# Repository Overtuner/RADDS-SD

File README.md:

# RADDS-SD
Adapter Board for RADDS

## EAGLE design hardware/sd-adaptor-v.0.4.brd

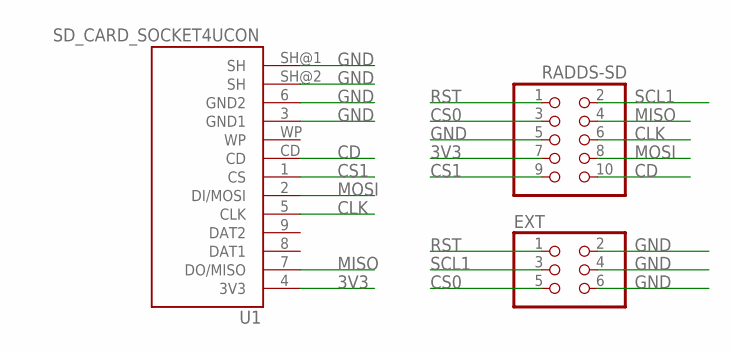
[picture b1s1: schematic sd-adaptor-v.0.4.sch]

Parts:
EXT: PINHD-2X3_2.54-SMD; 2X03SMD
RADDS-SD: PINHD-2X5_2.54-SMD; 2X05SMD
U1: SD_CARD_SOCKET4UCON; SDCARD_4UCONN

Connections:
3V3: RADDS-SD.7, U1.4 (3V3)
CD: RADDS-SD.10, U1.CD
CLK: RADDS-SD.6, U1.5 (CLK)
CS0: EXT.5, RADDS-SD.3
CS1: RADDS-SD.9, U1.1 (CS)
GND: EXT.2, EXT.4, EXT.6, RADDS-SD.5, U1.3 (GND1), U1.6 (GND2), U1.SH@1 (SH), U1.SH@2 (SH)
MISO: RADDS-SD.4, U1.7 (DO/MISO)
MOSI: RADDS-SD.8, U1.2 (DI/MOSI)
RST: EXT.1, RADDS-SD.1
SCL1: EXT.3, RADDS-SD.2

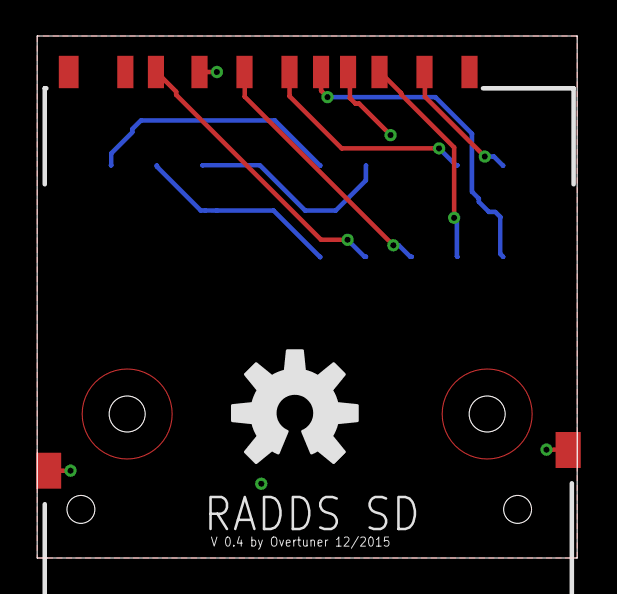
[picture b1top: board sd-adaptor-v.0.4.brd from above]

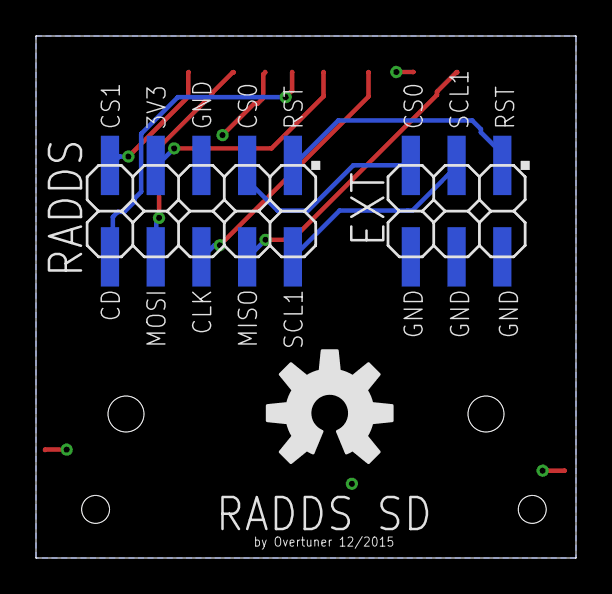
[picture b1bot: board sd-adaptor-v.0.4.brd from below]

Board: 2 copper layers, 30.0 x 29.0 mm, 5 parts (3 on the bottom side), 10 nets.

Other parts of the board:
U$1, U$3: OSHW-LOGO-L

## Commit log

2015-12-17 Eagle files
    untested
2016-01-30 1st batch
2016-01-30 front and back

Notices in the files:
parts and their libraries:
SparkFun-Connectors: Licensing: CC v3.0 Share-Alike You are welcome to use this library for commercial purposes.
